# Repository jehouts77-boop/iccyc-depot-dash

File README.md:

# ICCYC Depot Dashboard ("Control Console")

A desk instrument built as a Christmas gift for two friends: a railroad-flavoured
clock and information panel with a 4" square touchscreen, two round analog-style
gauges, a knob, four toggle switches, two pilot lights and a chime speaker, in a
3D-printed case with an engraved brass nameplate. ICCYC = a running
joke among friends.

**Status (2026-10-26):** every screen is built and has run on a real unit: the
screen ring, Home menu, knob, switches, chime schedule, gauges, Diagnostics,
WiFi setup, the on-screen settings, smooth text, the Overhead planes and ISS
pages (the ham-radio listener connects; a real ISS hearing hasn't shown on a
unit yet), BACK TO CLOCK, every month of On This Day, and checking GitHub for
updates (a real over-the-air update is still to be tested). The first console
is fully assembled on the hub PCB. Three units are being built for Christmas
2026; the case
and hub board files are in [`hardware/`](hardware/README.md).

This README is written so that someone - or an AI assistant - with no other
context can understand, change and extend the project.

## Hardware

| Part | Job |
|---|---|
| Pimoroni Presto (RP2350B, 480x480 touchscreen, WiFi) | Runs the app in `presto/`. Everything that might change lives here, because only the Presto can update over WiFi. |
| RP2040-Zero at I2C **0x10** ("Gauges") | Draws both round GC9A01 240x240 gauge screens. Firmware: `coproc/gauges/`. |
| RP2040-Zero at I2C **0x11** ("Controls") | Reads the EC11 knob (with push button) and 4 toggle switches, drives 2 pilot LEDs, plays WAV chime clips from its own flash through a MAX98357A amp. |
| Presto Qw/ST port (I2C0: SDA GP40, SCL GP41, 100 kHz) | The only link to both co-processors, shared bus. |
| Hub board (70 × 50 mm PCB) | Carries both Zeros and the amp in sockets, the pilot-light resistors, the 5 V rail; every wire leaves it on a pin header. Files: `hardware/hub-pcb/`. |
| Panel-mount USB-C socket, 5 V 3 A charger | Powers everything through one 5 V rail. **Unplug it before plugging a USB cable into any board inside.** |
| 4 toggle switches, 2 pilot lights, EC11 knob, CQRobot speaker, 2 × GC9A01 round screens | The panel. |
| Engraved brass nameplate | One per unit, with its serial number. |

Why co-processors: the Presto has no free GPIO pins - only the Qw/ST I2C port.
The co-processors have no WiFi, so their firmware is kept minimal ("dumb
instruments"): they only do what the Presto tells them over I2C. Updating them
means opening the case and plugging in USB.

The I2C register map is in [`docs/i2c-protocol.md`](docs/i2c-protocol.md).

## What it shows

Turn the knob (or tap PREV / NEXT at the bottom) to go round the screens:

- **Clock** - a railroad station clock: roman hours, a red 24-hour ring, a sweep second hand.
- **Weather** - the latest observation from the nearest airport weather station and the forecast (api.weather.gov).
- **Lantern Time** - sunrise, sunset and the countdown to dark, worked out on the device; moon phase.
- **On This Day** - one or two events from history for today's date (500+ entries for the year).
- **Nearest Train** - where the nearest Amtrak train is, how far, how fast and how late (Amtraker).
- **Overhead** - two pages, swapped with the button at the bottom right:
  - **PLANES** - a small radar-style scope and the nearest plane's flight, type, distance, height and speed (adsb.fi, with adsb.lol as a backup). Tap for the next plane.
  - **ISS** - where the International Space Station is right now (wheretheiss.at), how far, which way, and whether it's above the horizon; and when it was last heard over ham radio (see "The ISS radio" below).
- **Settings** - WiFi, chime, brightness, what the gauges show, BACK TO CLOCK, updates.

The two round gauges follow the screen (e.g. temperature and wind on the Clock,
altitude and direction to the plane on Overhead). Long-press the knob for
Diagnostics.

## The ISS radio (listen-only)

The console listens to APRS-IS, the internet side of ham radio's position
reporting system, for packets sent by the ISS's radio (callsign RS0ISS) or
relayed through it, and shows when it was last heard. It logs in with
passcode -1, which means **receive only: it never transmits anything**, so
no licence is needed to run it. Each unit needs its own login name in
`/config.json`: `{"iss": {"aprs_login": "..."}}` - a ham's own callsign, or
any name that isn't a callsign (the default is ICCYC1; give a second unit
ICCYC2, and so on). The ISS radio is often quiet for days.

## Files

```
presto/                 -> copy to the Presto's flash (root)
  main.py               starts app.py; shows and logs any crash, then restarts
  app.py                main loop: controls, touch, switches, chime, gauges, screens
  config.py             settings: DEFAULTS here, this unit's values in /config.json
  coproc.py             the Presto side of the I2C protocol (Gauges + Controls)
  gaugekinds.py         what a gauge can show (setup + which reading it follows)
  chime.py              when to chime; strike counts; mute rules
  timeutil.py           NTP, US Central time with daylight saving, time strings
  net.py                WiFi, memory-safe http_get, hand-scanning JSON helpers
  weather.py            api.weather.gov: latest observation + forecast (station/grid in config)
  sun.py                sunrise, sunset, twilight, sun direction, moon phase (pure maths)
  almanac.py            today's sun and moon for config "location", in local time
  fitz_data.py          words for screens/fitz.py (sources: data/fitz/fitzgerald_sources.md)
  trains.py             nearest Amtrak train from api-v3.amtraker.com (stations in config "train")
  planes.py             planes in the air near config "location" from adsb.fi, adsb.lol as backup (config "planes")
  iss.py                where the ISS is now, from wheretheiss.at (config "iss")
  aprs.py               reads APRS (ham radio) packets: positions in all three formats, objects, text
  isslisten.py          the always-on listen-only APRS-IS connection for the ISS page
  otd.py                On This Day: reads otd_data/MM.json (current month only)
  ota.py                over-the-air updates from GitHub (see Updates below)
  otaguard.py           undoes an update that was cut short or keeps crashing; never updated itself
  otd_data/             On This Day entries, one JSON file per month (built - don't edit)
  textutil.py           ascii_safe, word_wrap
  ui.py                 colours, header/footer, smooth text (PicoVector) and the built-in font
  fonts/                the two .af font files - copy them to the Presto's / (see fonts/README.md)
  screens/              one file per screen; the ring order is in screens/__init__.py
coproc/gauges/          -> copy to the 0x10 board: main.py + drivers/
coproc/controls/        -> copy to the 0x11 board: main.py + clips/ as /clips (see its README)
hardware/               the case (OpenSCAD + STLs), the hub board (KiCad + Gerbers), the wiring - see hardware/README.md
docs/i2c-protocol.md    register map and rules for the I2C link
data/otd/otd_master.csv On This Day master list: one row per event, with its source link
tools/build_otd.py      builds presto/otd_data/ from the master list (python tools/build_otd.py)
tools/make_chimes.py    makes the synthesised whistle clip in coproc/controls/clips/ (needs numpy + scipy)
tools/cut_bell.py       cuts the bell clip from data/chimes/freesound_591868_... (CC0 recording; needs ffmpeg)
tools/build_telegraph.py cuts the telegraph clips from data/chimes/sounder_recording_2026-10-10.wav (Jason's own sounder)
```

## Updates (over the air)

A unit updates itself from GitHub: every night at 03:30 it asks for the list
of files on the branch it follows (config `"ota"`: `repo`, `branch`, `auto`,
`time`), downloads only the files under `presto/` that differ from its own
(`.py`, `.json`, `.af`), checks each one (size, git fingerprint, and that a
`.py` file compiles), swaps them in and restarts. Settings > UPDATES shows the
state and has CHECK NOW and PUT BACK OLD.

- **Units follow the `release` branch, not `main`.** `main` is the working
  branch. To publish: confirm a commit on a real unit, then
  `git push origin <that commit>:release`.
- No password is used, so the repo must be public for updates to work.
- `main.py` and `otaguard.py` are never updated (they are the safety net: an
  update that is interrupted, or that crashes twice at start-up, is undone
  automatically and that version is skipped until a newer one is published).
  Changing either of them means a USB cable.
- `/config.json` and `secrets.py` are never touched. Files deleted from the
  repo stay on the unit.
- On a unit you load by USB during development, put `{"ota": {"auto": false}}`
  in its `/config.json`, or the nightly update will put the released files
  back over your newer ones.
- In a fork: point `ota.repo` at the fork and create a `release` branch there.

## Per-unit settings (never overwritten by updates)

`/config.json` on the Presto holds only what differs from `DEFAULTS` in
`config.py`: WiFi, unit serial, and anything changed on the Settings screen.
Updates replace the engine files but never this file.

To make a fork yours, put these in `/config.json` (the defaults are for
Wentzville, Missouri): `location` (name, lat, lon), `tz`, `weather` (`station`
and `grid` - look them up for your location at api.weather.gov/points/LAT,LON),
`train` (`stations`, `watch` - Amtrak station codes), `planes.radius_mi`,
`iss.aprs_login`, and `ota.repo` if you update from your own fork.

WiFi is set on the unit itself (`presto/screens/wifi.py`): a unit with no
WiFi saved opens a welcome page at start-up, and the WIFI row on the Settings
screen reopens it - pick a network, type the password on the touch keyboard
(or with the knob), and it is saved to `/config.json`.

During development, WiFi can instead come from a `secrets.py` on the Presto
(see `secrets.py.example`). It is listed in `.gitignore`; never commit it.

## Controls

- **Knob:** turn = previous / next screen; press = Home menu (turn to pick,
  press to open); long press (0.8 s) = Diagnostics and back.
- **Touch:** tap a Home menu row, or PREV / MENU / NEXT along the bottom. On
  Overhead, tap the scope area for the next plane and the button at the bottom
  right to swap PLANES / ISS. (The
  Clock fills the whole screen and doesn't draw that strip, but the bottom of
  the screen still works the same way: left, middle, right.)
- Untouched for `idle_s` (default 3 minutes) -> back to the Clock.
- **Switches** (up = on; DAY · NIGHT: up = day, down = night). In the code a
  closed switch = the non-normal state, and `switch_invert` (one bit per switch:
  1 CHIME, 2 DAY·NIGHT, 4 BACKLIGHT, 8 WIFE MODE) flips any that end up
  upside-down at assembly. With the toggles mounted as in this panel (each closes when
  up), up = on needs `"switch_invert": 7` in `/config.json`. CHIME mutes the chime; DAY/NIGHT picks day or night brightness (manual, no
  automatic dimming); BACKLIGHT turns the Presto and gauge screens off and dims
  the pilot lights (the clock and chime keep running); WIFE MODE mutes the
  chime and uses night brightness, with no on-screen announcement.
- **Chime modes:** off / hourly / hourly_count (plus one strike per hour) /
  half_hourly; quiet hours (default 22:00-07:00).

## Gauges follow the screen

Each screen names its two gauges in `config.py` -> `"gauges"`, using kinds from
`gaugekinds.py`. A kind whose reading isn't available yet rests at its start
with the number hidden.

## Getting it onto a Presto (by USB)

1. Flash Pimoroni's MicroPython for the Presto, if it isn't already on it.
2. With Thonny (or `mpremote`), copy everything in `presto/` to the Presto's
   root, keeping the folders (`screens/`, `otd_data/`, `fonts/`).
3. Copy `coproc/gauges/` to the 0x10 board and `coproc/controls/` (with its
   `clips/`) to the 0x11 board, each as `main.py` at the board's root.
4. Restart the Presto. With no WiFi saved it opens the WiFi page: pick your
   network and type the password. If you will keep loading files by USB, also
   set `{"ota": {"auto": false}}` in `/config.json` (see Updates above).

## Data sources

Weather: [api.weather.gov](https://api.weather.gov) (US National Weather Service).
Trains: [Amtraker](https://amtraker.com). Planes: [adsb.fi](https://adsb.fi)
open data (personal, non-commercial use), with [adsb.lol](https://adsb.lol) as
a backup. ISS position: [wheretheiss.at](https://wheretheiss.at). ISS radio:
[APRS-IS](https://www.aprs-is.net), listen-only.

## Licence

MIT - see `LICENSE`. The GC9A01 display driver in `coproc/gauges/drivers/` is
Peter Hinch's micropython-nano-gui driver (MIT, see its licence file there).
Fonts: Barlow / Barlow Condensed (SIL Open Font License) and Special Elite
(Apache 2.0) - licence files beside them in `presto/fonts/` and
`hardware/enclosure/fonts/`. The telegraph chime is the builder's own recording.

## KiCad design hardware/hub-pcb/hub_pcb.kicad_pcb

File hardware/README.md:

# Hardware: the case, the hub board and the wiring

Everything needed to build the physical console, as it stood on 2026-10-14.
The software is in the rest of the repo (see the main `README.md`).

These files were copied from the builder's working folder; the `.md` files in
here are working logs as much as guides, with dates and decisions as they
happened. Where a file says "roadmap 4.1a" or similar, that is the builder's
own plan, which isn't in this repo.

## `enclosure/` - the 3D-printed case (OpenSCAD)

| File | What it makes |
|---|---|
| `common.scad` | every shared measurement: the Presto, gauges, knob, switches, speaker, the tilt (8°) - change sizes here |
| `body.scad` | the case body (rev E): box with a sloped front, removable back plate, corner screw bosses for M3 heat-set inserts |
| `panel.scad` | the front panel (rev E): screen window, two gauge holes, knob, the switch row and pilot lights, the inlaid labels |
| `parts.scad` | the small parts: P1 hub shelf, P2 speaker strap, P3 gauge retainers, P4 knob |
| `bezels.scad` | P5 screen frame, P6 gauge rings, P7 knob ring |
| `coupons.scad` | small test pieces for checking fits before a full print |
| `wood_grain.py` | adds the carved wood-grain texture to the body: `python wood_grain.py body_plain.stl body_grain.stl` (needs numpy, trimesh, manifold3d) |
| `fonts/` | the label font (Barlow SemiBold, SIL Open Font License - `Barlow-OFL.txt`); OpenSCAD finds it through the `use <fonts/...>` line |
| `revE_mockup_2026-10-09.png` | what rev E looks like |

To make an STL: open the `.scad` in OpenSCAD, render (F6), export. The
`.scad` files are written as seen from the FRONT, so left and right swap when
you look at the back of the panel.

### `enclosure/stl/` - ready to print (current revisions)

| File | Notes |
|---|---|
| `body_revE_wood_print.3mf` | the body with the wood grain (printed in wood PLA). Back face down, brim, no supports |
| `body_revE_plain_print.stl` | the same body without the grain |
| `back_plate_revE_print.stl` | removable back plate (printed black); sits 2 mm into the body, 4 × M3 × 8 screws, holds the USB-C power socket |
| `panel_revE_print.stl` + `panel_labels_revE_print.stl` | the front panel and its inlaid labels: load both together in Bambu Studio as one object with two parts (labels part = cream filament, panel = black); supports on the build plate under the three front recesses |
| `p1_hub_shelf_revE2_print.stl` | the shelf the hub board sits on, behind the Presto (rev E2: a roomier pocket for the rev A board) |
| `parts_revD5_print.stl` | all the small parts on one plate |
| `p3_gauge_retainers_revD5_print.stl`, `p4_knob_fluted_revD4_print.stl` | the gauge retainers and the knob on their own |
| `bezels_revD_print.stl`, `p5_screen_frame_revD_print.stl`, `p6_gauge_ring_revD_print.stl`, `p7_knob_ring_revD_print.stl` | the bezels, all together or one by one |

Printed on Bambu Lab printers at 0.2 mm layers. Hardware: M3 heat-set inserts
(8 in the body) and M3 × 8 screws.

## `hub-pcb/` - the hub board

A small 70 × 50 mm two-layer board that sits behind the Presto. It carries the
two RP2040-Zeros (0x10 gauges, 0x11 controls) and the MAX98357A amp in female
header sockets, the two 330 Ω resistors for the pilot lights, one +5 V rail and
ground, and a pin header (or JST-PH socket) for every wire that leaves the
board.

| File | What it is |
|---|---|
| `hub_pcb_revA_gerbers.zip` | **the order files** - upload this to a board maker (rev A was made by OSH Park) |
| `hub-pcb-parts-list.md` | what to buy to populate it, with part numbers |
| `hub-board-build.md` | what goes where, every off-board wire, and the build log |
| `hub-revA-rework.md` | **read first: three corrections rev A needs** (6 wires for the Zeros' bottom row, the PRESTO socket turned round, sand the edge nubs), with `hub_revA_rework_wires.png` |
| `hub-pcb-solder-guide.md` | **how to solder and check the board**, step by step, with pictures (in `hub-pcb-solder-guide/`) |
| `hub_pcb_steps.py` | draws those pictures from `hub_pcb.kicad_pcb` (needs matplotlib only, not KiCad): `python hub_pcb_steps.py` |
| `hub_pcb_copper.png`, `hub_pcb_kicad_view.png`, `hub_pcb_placement.png` | pictures of the board |
| `hub_layout.py` | the netlist in practice: every connection and hole, with checks; writes `hub_holes.json` and `hub-board-layout.png` |
| `hub_pcb.py` | builds the KiCad board from `hub_layout.py`'s output, routes it (`hub_router.py`), runs KiCad's design-rule check, draws the pictures and writes the Gerbers. Needs KiCad 7's Python module (`pcbnew`). Run `python hub_layout.py` first, then `python hub_pcb.py` |
| `hub_pcb.kicad_pcb`, `hub_pcb.kicad_pro` | the board itself, openable in KiCad |
| `hub_pcb_report.txt` | the checks from the last build |

**Check the power socket polarity with a meter before the first power-up.**
JST-PH sockets on this board are pin 1 = ground, pin 2 = +5 V.

## `wiring/`

`wiring-plan.md` - power (one panel-mount USB-C socket feeding a single 5 V
rail) and the full wire lists for both co-processors; `wiring-diagram.svg` -
the picture.

## The rule that matters most

**Unplug the case's power before plugging a USB cable into anything inside.**
The USB-C socket feeds the 5 V rail directly, and so does a computer's USB.

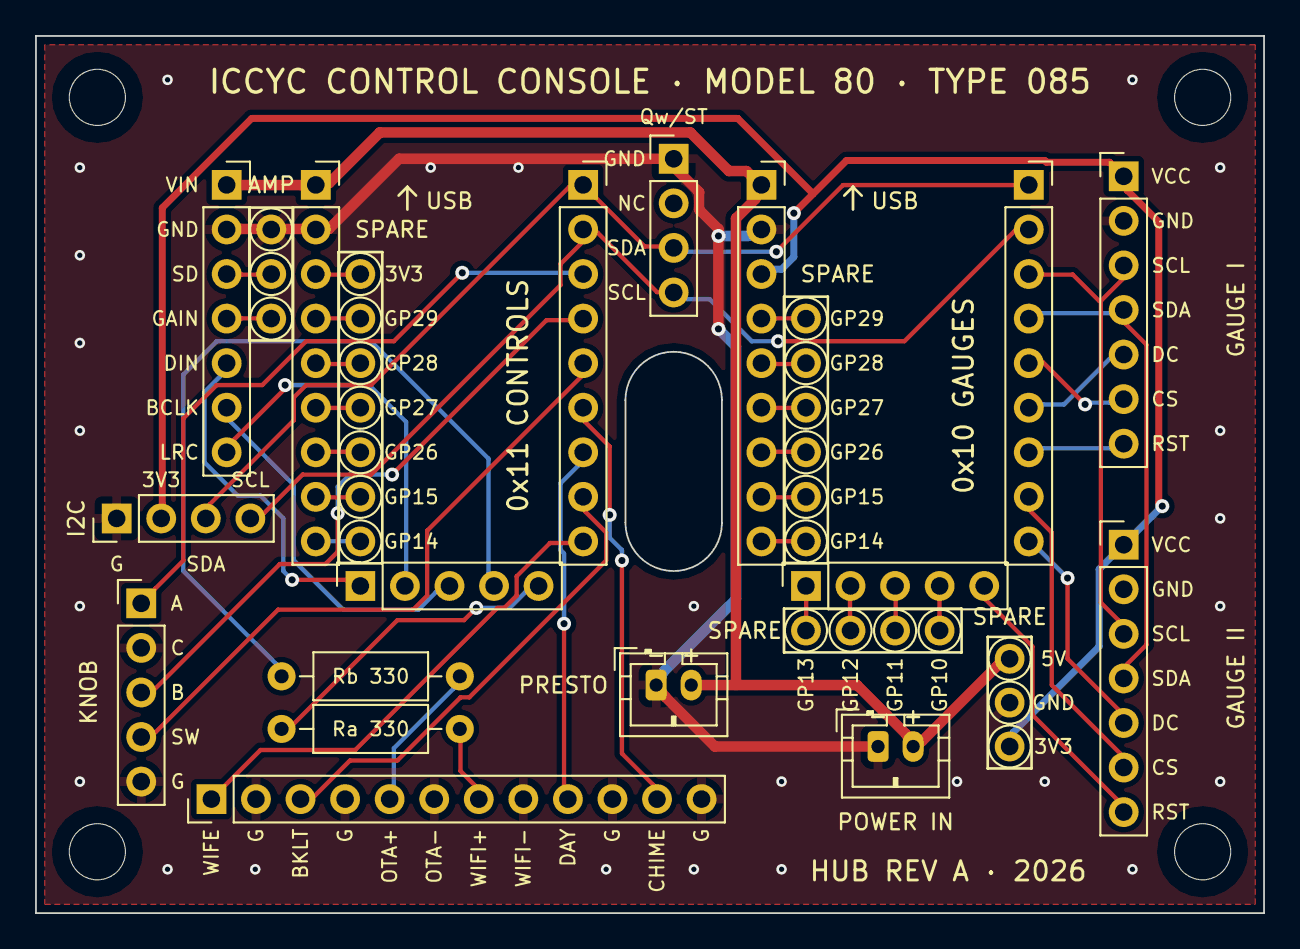
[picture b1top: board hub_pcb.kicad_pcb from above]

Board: 2 copper layers, 70.0 x 50.0 mm, 44 parts (0 on the bottom side), 46 nets.

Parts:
H1, H2, H3, H4: MountingHole_3.2mm_M3
J10B: 0x10 bottom; PinSocket_1x05_P2.54mm_Vertical
J10L: 0x10 left; PinSocket_1x09_P2.54mm_Vertical
J10R: 0x10 right; PinSocket_1x09_P2.54mm_Vertical
J11B: 0x11 bottom; PinSocket_1x05_P2.54mm_Vertical
J11L: 0x11 left; PinSocket_1x09_P2.54mm_Vertical
J11R: 0x11 right; PinSocket_1x09_P2.54mm_Vertical
JAMP: amp; PinSocket_1x07_P2.54mm_Vertical
JCTRL: SWITCHES + LIGHTS; PinHeader_1x12_P2.54mm_Vertical
JG1: GAUGE I; PinHeader_1x07_P2.54mm_Vertical
JG2: GAUGE II; PinHeader_1x07_P2.54mm_Vertical
JI2C: I2C add-on; PinHeader_1x04_P2.54mm_Vertical
JKNOB: KNOB; PinHeader_1x05_P2.54mm_Vertical
JPRESTO: PRESTO battery lead; JST_PH_B2B-PH-K_1x02_P2.00mm_Vertical
JPWR: POWER IN (xiwai lead); JST_PH_B2B-PH-K_1x02_P2.00mm_Vertical
JQW: Qw/ST; PinHeader_1x04_P2.54mm_Vertical
RA: 330R WiFi; R_Axial_DIN0207_L6.3mm_D2.5mm_P10.16mm_Horizontal
RB: 330R OTA; R_Axial_DIN0207_L6.3mm_D2.5mm_P10.16mm_Horizontal
S10_GP10, S10_GP11, S10_GP12, S10_GP13, S10_GP14, S10_GP15, S10_GP26, S10_GP27, S10_GP28, S10_GP29, S11_3V3, S11_GP14, S11_GP15, S11_GP26, S11_GP27, S11_GP28, S11_GP29: spare; TestPoint_THTPad_D2.0mm_Drill1.0mm
SP_3V3, SP_5V: spare; TestPoint_THTPad_D2.0mm_Drill1.0mm
SP_AMP_GAIN: spare; TestPoint_THTPad_D2.0mm_Drill1.0mm
SP_AMP_GND: spare; TestPoint_THTPad_D2.0mm_Drill1.0mm
SP_AMP_SD: spare; TestPoint_THTPad_D2.0mm_Drill1.0mm
SP_GND: spare; TestPoint_THTPad_D2.0mm_Drill1.0mm

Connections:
0x10_GP10: J10B.4, S10_GP10.1
0x10_GP11: J10B.3, S10_GP11.1
0x10_GP12: J10B.2, S10_GP12.1
0x10_GP13: J10B.1, S10_GP13.1
0x10_GP14: J10L.9, S10_GP14.1
0x10_GP15: J10L.8, S10_GP15.1
0x10_GP26: J10L.7, S10_GP26.1
0x10_GP27: J10L.6, S10_GP27.1
0x10_GP28: J10L.5, S10_GP28.1
0x10_GP29: J10L.4, S10_GP29.1
0x11_3V3: J11L.3, S11_3V3.1
0x11_GP14: J11L.9, S11_GP14.1
0x11_GP15: J11L.8, S11_GP15.1
0x11_GP26: J11L.7, S11_GP26.1
0x11_GP27: J11L.6, S11_GP27.1
0x11_GP28: J11L.5, S11_GP28.1
0x11_GP29: J11L.4, S11_GP29.1
3V3_G: J10L.3, JG1.1, JG2.1, JI2C.2, SP_3V3.1
+5V: J10L.1, J11L.1, JAMP.1, JPRESTO.2, JPWR.2, SP_5V.1
AMP_GAIN: JAMP.4, SP_AMP_GAIN.1
AMP_SD: JAMP.3, SP_AMP_SD.1
BCLK: J11B.3, JAMP.6
CS1: J10R.5, JG1.6
CS2: J10R.8, JG2.6
DC1: J10R.6, JG1.5
DC2: J10R.9, JG2.5
DIN: J11B.1, JAMP.5
ENC_A: J11R.3, JKNOB.1
ENC_B: J11R.4, JKNOB.3
ENC_SW: J11R.5, JKNOB.4
GND: J10L.2, J11L.2, JAMP.2, JCTRL.2, JCTRL.4, JCTRL.6, JCTRL.8, JCTRL.10, JCTRL.12, JG1.2, JG2.2, JI2C.1, JKNOB.2, JKNOB.5, JPRESTO.1, JPWR.1, JQW.1, SP_AMP_GND.1, SP_GND.1
LED_OTA: JCTRL.5, RB.2
LED_OTA_R: J11B.4, RB.1
LED_WIFI: JCTRL.7, RA.2
LED_WIFI_R: J11B.5, RA.1
LRC: J11B.2, JAMP.7
MOSI: J10R.4, JG1.4, JG2.4
RST1: J10R.7, JG1.7
RST2: J10B.5, JG2.7
SCK: J10R.3, JG1.3, JG2.3
SCL: J10R.2, J11R.2, JI2C.4, JQW.4
SDA: J10R.1, J11R.1, JI2C.3, JQW.3
SW_BACKLIGHT: J11R.8, JCTRL.3
SW_CHIME: J11R.6, JCTRL.11
SW_DAYNIGHT: J11R.7, JCTRL.9
SW_WIFEMODE: J11R.9, JCTRL.1

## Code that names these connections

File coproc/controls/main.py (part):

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ADDR = 0x11
FW_MAJOR, FW_MINOR = 0, 5

PIN_ENC_A = 2
PIN_ENC_B = 3
PIN_BTN = 4
SWITCH_PINS = (5, 6, 7, 8)     # bit 0 CHIME, 1 DAY-NIGHT, 2 BACKLIGHT, 3 WIFE MODE
LED_PINS = (29, 28)            # WiFi, OTA   (fw 0.3: 9, 10)
PIN_BCLK, PIN_LRC, PIN_DIN = 26, 27, 15   # LRC must be BCLK + 1 (RP2040 rule)   (fw 0.3: 11, 12, 13)

STEPS_PER_DETENT = 4   # confirmed 2026-09-30: one click = 1
ENC_REVERSE = False    # confirmed 2026-09-30: clockwise counts up
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# ---- Encoder: quadrature decoding in a hard interrupt ----
# The two encoder pins (A, B) switch in a fixed order as the knob turns. The
# table maps (previous state, new state) -> +1, -1 or 0 (0 = bounce/invalid).
pin_a = Pin(PIN_ENC_A, Pin.IN, Pin.PULL_UP)
pin_b = Pin(PIN_ENC_B, Pin.IN, Pin.PULL_UP)
_QTABLE = (0, -1, 1, 0, 1, 0, 0, -1, -1, 0, 0, 1, 0, 1, -1, 0)
_enc_state = (pin_a.value() << 1) | pin_b.value()
enc_steps = 0
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    buf_ms = IBUF * 1000 // (rate * 2)
    mem[R_DIAG_BUF_MS] = min(255, buf_ms)
    mem[R_DIAG_GAP_MS] = 0
    audio = I2S(0, sck=Pin(PIN_BCLK), ws=Pin(PIN_LRC), sd=Pin(PIN_DIN),
                mode=I2S.TX, bits=16, format=I2S.MONO, rate=rate, ibuf=IBUF)
    audio.irq(_refill)                  # from now on, writes don't wait
    active = True
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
